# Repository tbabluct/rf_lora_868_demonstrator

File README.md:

# rf_lora_868_demonstrator
Demonstrator electrical design and software for UCT's EEE3097S course of 2020

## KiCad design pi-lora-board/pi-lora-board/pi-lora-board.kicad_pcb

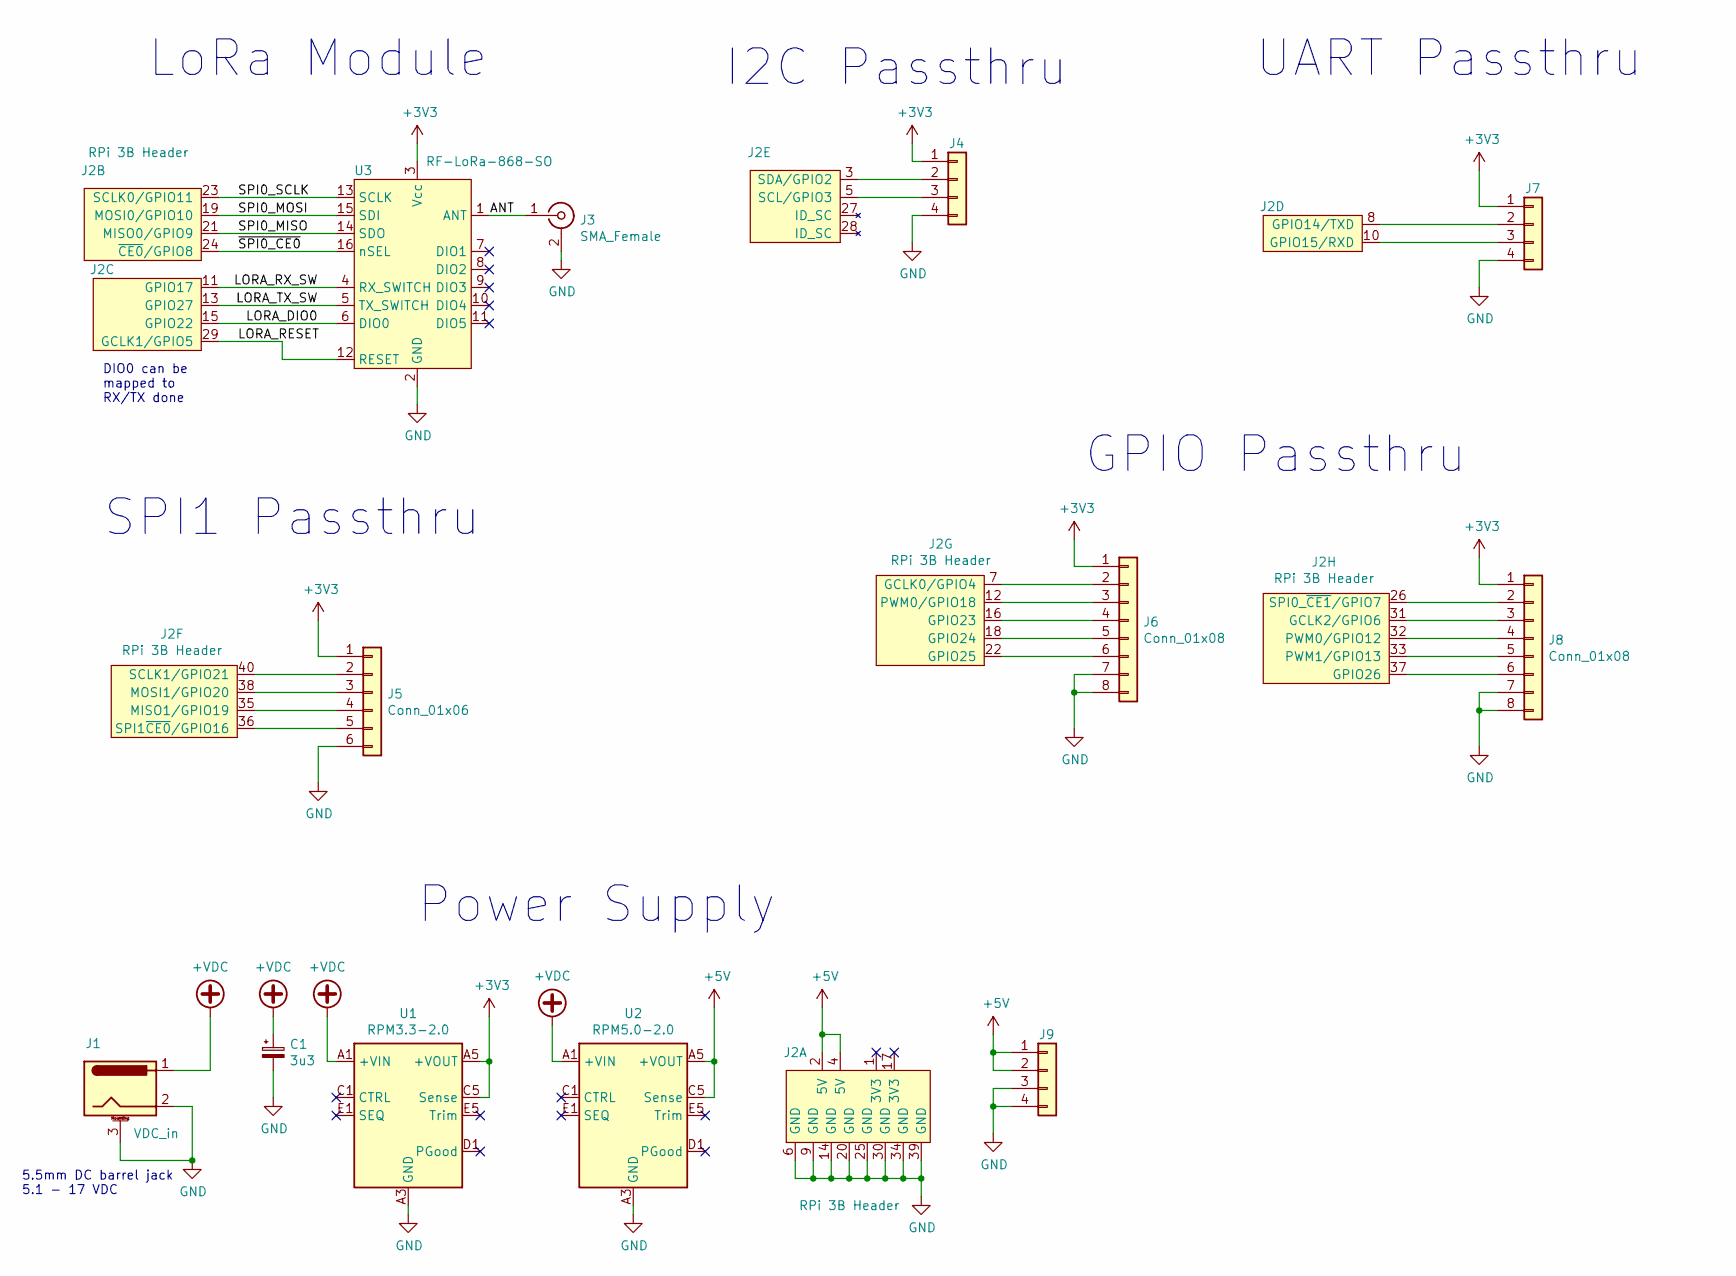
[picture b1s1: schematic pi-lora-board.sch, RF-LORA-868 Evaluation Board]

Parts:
C1: 3u3; CP_Radial_D5.0mm_P2.00mm
J1: VDC_in; BarrelJack_Wuerth_6941xx301002
J2: RPi 3B Header; PinSocket_2x20_P2.54mm_Vertical
J3: SMA_Female; RS-PRO-EdgeMount-SMA
J4, J7, J9: Conn_01x04; PinHeader_1x04_P2.54mm_Vertical
J5: Conn_01x06; PinHeader_1x06_P2.54mm_Vertical
J6, J8: Conn_01x08; PinHeader_1x08_P2.54mm_Vertical
U1: RPM3.3-2.0; Converter_DCDC_RECOM_RPMx.x-x.0
U2: RPM5.0-2.0; Converter_DCDC_RECOM_RPMx.x-x.0
U3: RF-LoRa-868-SO; LoRa-16

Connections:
+3V3: J4.1, J5.1, J6.1, J7.1, J8.1, U1.A5 (+VOUT), U1.B5 (+VOUT), U1.C5 (Sense), U3.3 (Vcc)
+5V: J2.2 (5V), J2.4 (5V), J9.1, J9.2, U2.A5 (+VOUT), U2.B5 (+VOUT), U2.C5 (Sense)
+VDC: C1.1, J1.1, U1.A1 (+VIN), U1.A2 (+VIN), U2.A1 (+VIN), U2.A2 (+VIN)
/ANT: J3.1 (In), U3.1 (ANT)
/LORA_DIO0: J2.15 (GPIO22), U3.6 (DIO0)
/LORA_RESET: J2.29 (GCLK1/GPIO5), U3.12 (RESET)
/LORA_RX_SW: J2.11 (GPIO17), U3.4 (RX_SWITCH)
/LORA_TX_SW: J2.13 (GPIO27), U3.5 (TX_SWITCH)
/SPI0_MISO: J2.21 (MISO0/GPIO9), U3.14 (SDO)
/SPI0_MOSI: J2.19 (MOSI0/GPIO10), U3.15 (SDI)
/SPI0_SCLK: J2.23 (SCLK0/GPIO11), U3.13 (SCLK)
/~SPI0_CE0: J2.24 (~CE0~/GPIO8), U3.16 (nSEL)
GND: C1.2, J1.2, J1.3 (MountPin), J2.6 (GND), J2.9 (GND), J2.14 (GND), J2.20 (GND), J2.25 (GND), J2.30 (GND), J2.34 (GND), J2.39 (GND), J3.2 (Ext), J4.4, J5.6, J6.7, J6.8, J7.4, J8.7, J8.8, J9.3, J9.4, U1.A3 (GND), U1.A4 (GND), U1.B1 (GND), U1.B2 (GND), U1.B3 (GND), U1.B4 (GND), U1.C2 (GND), U1.C3 (GND), U1.C4 (GND), U1.D2 (GND), U1.D3 (GND), U1.D4 (GND), U1.D5 (GND), U1.E3 (GND), U1.E4 (GND), U2.A3 (GND), U2.A4 (GND), U2.B1 (GND), U2.B2 (GND), U2.B3 (GND), U2.B4 (GND), U2.C2 (GND), U2.C3 (GND), U2.C4 (GND), U2.D2 (GND), U2.D3 (GND), U2.D4 (GND), U2.D5 (GND), U2.E3 (GND), U2.E4 (GND), U3.2 (GND)
unnamed: J2.3 (SDA/GPIO2), J4.2
unnamed: J2.5 (SCL/GPIO3), J4.3
unnamed: J2.7 (GCLK0/GPIO4), J6.2
unnamed: J2.8 (GPIO14/TXD), J7.2
unnamed: J2.10 (GPIO15/RXD), J7.3
unnamed: J2.12 (PWM0/GPIO18), J6.3
unnamed: J2.16 (GPIO23), J6.4
unnamed: J2.18 (GPIO24), J6.5
unnamed: J2.22 (GPIO25), J6.6
unnamed: J2.26 (SPI0_~CE1~/GPIO7), J8.2
unnamed: J2.31 (GCLK2/GPIO6), J8.3
unnamed: J2.32 (PWM0/GPIO12), J8.4
unnamed: J2.33 (PWM1/GPIO13), J8.5
unnamed: J2.35 (MISO1/GPIO19), J5.4
unnamed: J2.36 (SPI1~CE0~/GPIO16), J5.5
unnamed: J2.37 (GPIO26), J8.6
unnamed: J2.38 (MOSI1/GPIO20), J5.3
unnamed: J2.40 (SCLK1/GPIO21), J5.2

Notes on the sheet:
DIO0 can be mapped to RX/TX done
5.5mm DC barrel jack 5.1 - 17 VDC
Power Supply
LoRa Module
I2C Passthru
UART Passthru
SPI1 Passthru
GPIO Passthru

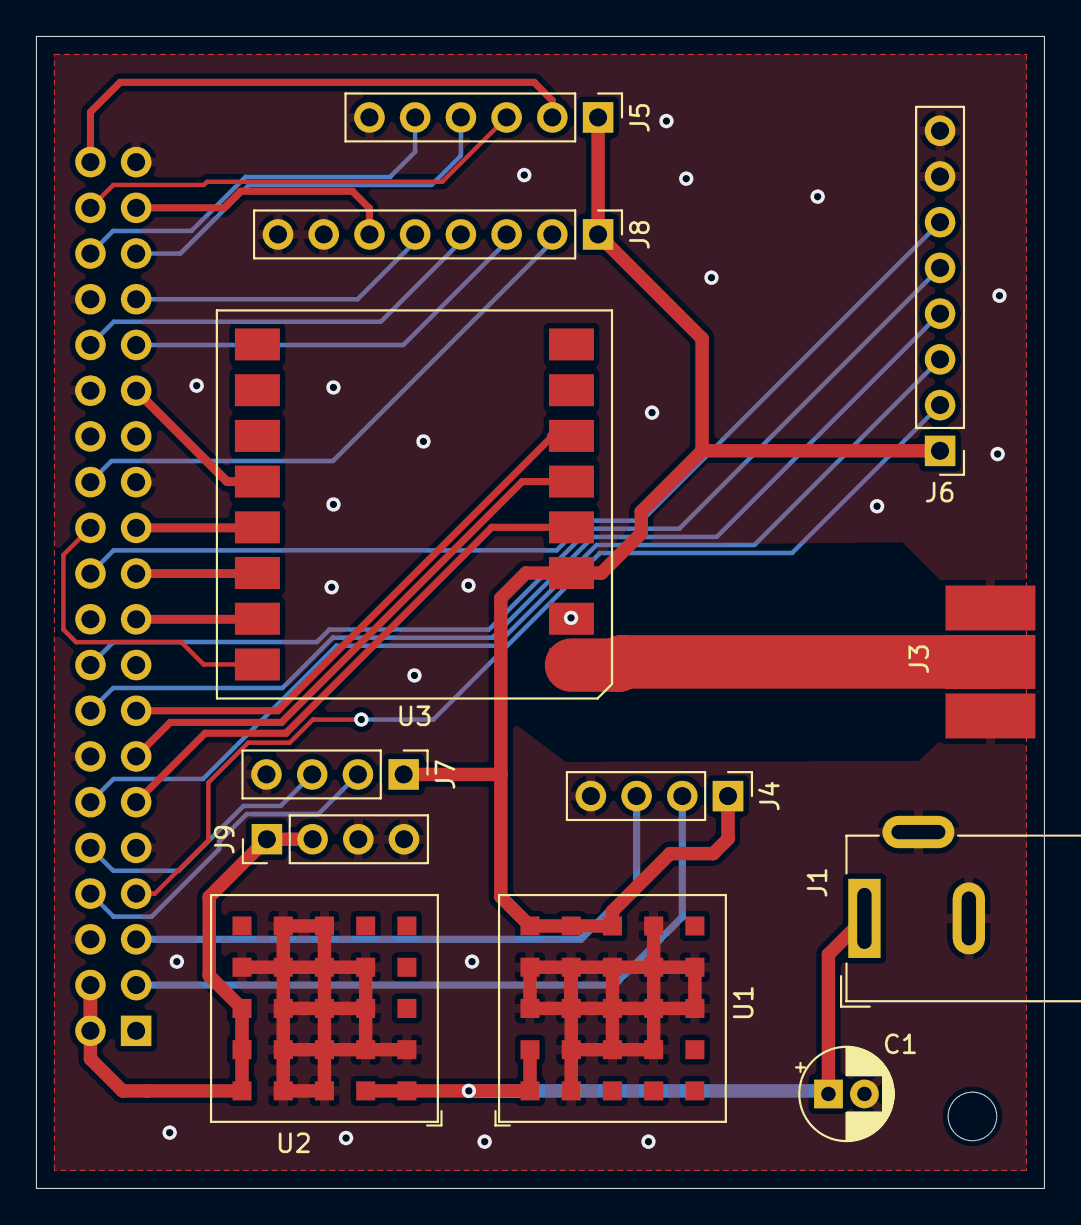
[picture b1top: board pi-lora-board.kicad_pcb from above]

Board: 2 copper layers, 56.0 x 64.0 mm, 13 parts (1 on the bottom side), 31 nets.

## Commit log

2020-11-05 Add demonstator designs and programs
